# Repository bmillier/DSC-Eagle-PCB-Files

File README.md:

# DSC-Eagle-PCB-Files
Eagle PCB and schematic files
These are the BRD and SCH files for the Arduino Shield, as well as the BRD file for the small PCB used for the DSC thermal head.
I had the Arduino Shield PCB fabricated at Osh Park Sales- 3 boards cost USD35

The DSC thermal head PCB is a PCB that I have used on previous DSC models, and was originally fabricated by Express PCB, using their own PCB 
software.
I have drawn this PCB in Eagle, and have included that file, although I have not had this board fabricated from this file yet.

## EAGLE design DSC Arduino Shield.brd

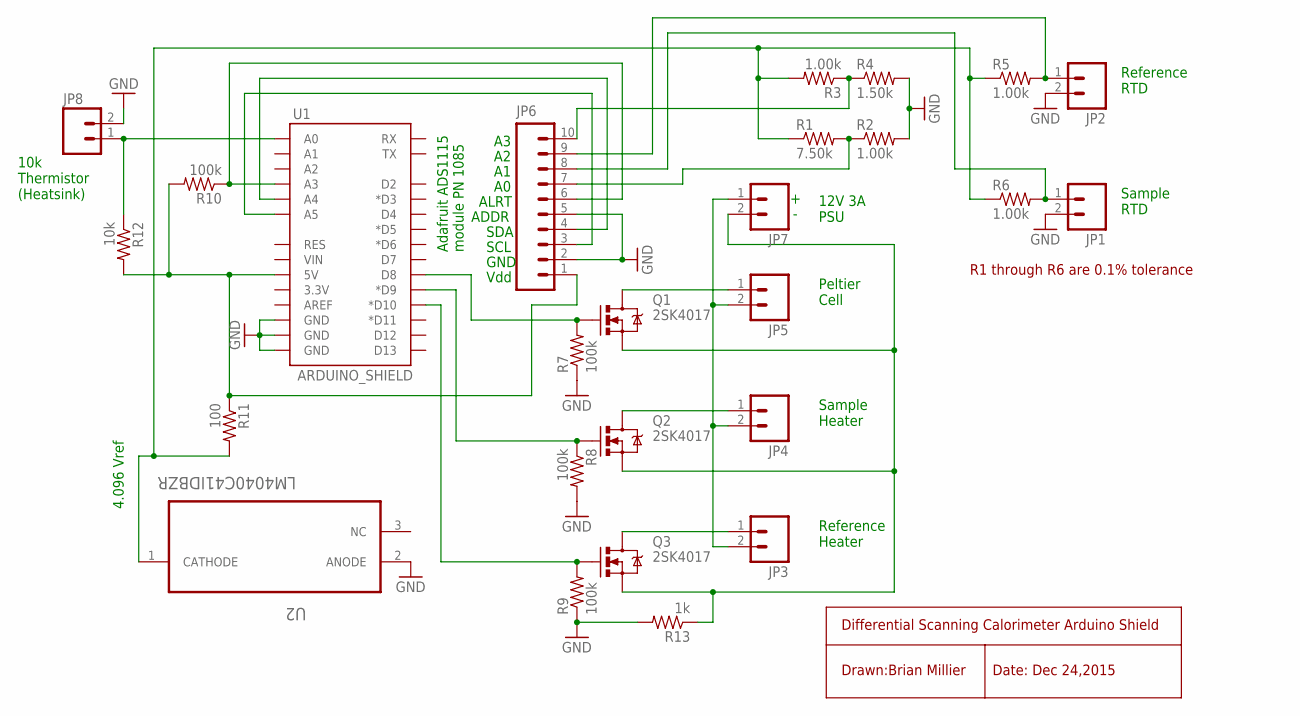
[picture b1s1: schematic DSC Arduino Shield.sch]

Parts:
JP1, JP2, JP3, JP4, JP5, JP7, JP8: M023.5MM_LOCK; SCREWTERMINAL-3.5MM-2_LOCK
JP6: M10SILK_FEMALE_PTH; 1X10
Q1, Q2, Q3: 2SK4017; DPAK
R1: 7.50k; AXIAL-0.3
R2, R3, R5, R6: 1.00k; AXIAL-0.3
R4: 1.50k; AXIAL-0.3
R7, R8, R9, R10: 100k; AXIAL-0.3
R11: 100; AXIAL-0.3
R12: 10k; AXIAL-0.3
R13: 1k; AXIAL-0.3
U1: ARDUINO_SHIELD; DUEMILANOVE_VIAS
U2: LM4040C41IDBZR; SOT95P237X112-3N

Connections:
GND: JP1.2, JP2.2, JP6.2, JP6.5, JP8.2, R2.P$2 (2), R4.P$2 (2), R7.P$1 (1), R8.P$2 (2), R9.P$1 (1), R13.P$2 (2), U1.GND@0 (GND), U1.GND@1 (GND), U1.GND@2 (GND), U2.2 (ANODE)
unnamed: Q1.1 (G), R7.P$2 (2), U1.D8
unnamed: Q2.1 (G), R8.P$1 (1), U1.D9 (*D9)
unnamed: Q3.1 (G), R9.P$2 (2), U1.D10 (*D10)
unnamed: JP5.1, Q1.4 (D)
unnamed: JP4.1, Q2.4 (D)
unnamed: JP3.1, Q3.4 (D)
unnamed: JP3.2, JP4.2, JP5.2, JP7.1
unnamed: JP6.7, R1.P$2 (2), R2.P$1 (1)
unnamed: JP6.10, R3.P$1 (1), R4.P$1 (1)
unnamed: JP6.1, R10.P$2 (2), R11.P$1 (1), R12.P$2 (2), U1.5V
unnamed: JP7.2, Q1.3 (S), Q2.3 (S), Q3.3 (S), R13.P$1 (1)
unnamed: JP6.3, U1.A5
unnamed: JP6.4, U1.A4
unnamed: JP6.6, R10.P$1 (1), U1.A3
unnamed: JP2.1, JP6.9, R5.P$2 (2)
unnamed: R1.P$1 (1), R3.P$2 (2), R5.P$1 (1), R6.P$1 (1), R11.P$2 (2), U2.1 (CATHODE)
unnamed: JP1.1, JP6.8, R6.P$2 (2)
unnamed: JP8.1, R12.P$1 (1), U1.A0

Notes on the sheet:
Peltier Cell
Sample Heater
Reference Heater
12V 3A PSU
Sample RTD
Reference RTD
10k Thermistor (Heatsink)
Adafruit ADS1115 module PN 1085
Vdd
GND
SCL
SDA
ADDR
ALRT
4.096 Vref
Differential Scanning Calorimeter Arduino Shield
Date: Dec 24,2015
Drawn:Brian Millier
R1 through R6 are 0.1% tolerance

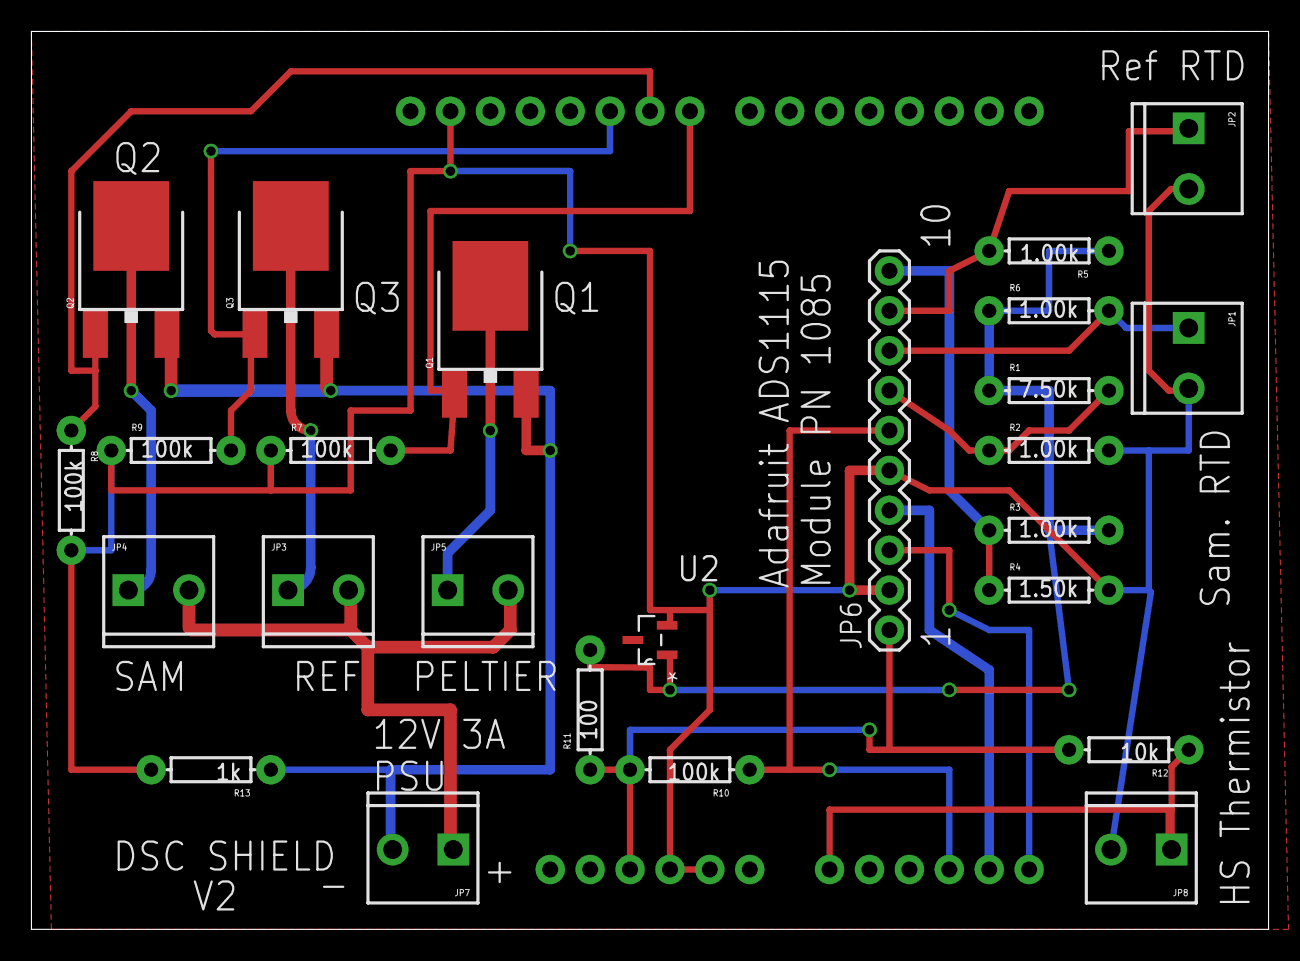
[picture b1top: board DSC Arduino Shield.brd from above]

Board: 2 copper layers, 78.7 x 57.1 mm, 26 parts (0 on the bottom side), 19 nets.

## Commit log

2016-05-31 :lollipop: Added .gitattributes & .gitignore files
2016-05-31 Eagle PCB/schematic files
    Eagle PCB & Schematic files for Arduino Shield
    Eagle PCB file for DSC Thermal head

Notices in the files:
parts and their libraries:
SparkFun-Boards: Licensing: Creative Commons ShareAlike 4.0 International - https://creativecommons.org/licenses/by-sa/4.0
